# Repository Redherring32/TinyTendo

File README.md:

# Tiny 'Tendo
An open-source Gameboy sized handheld NES using real hardware

## DISCLAIMER:

TinyTendo is a complex project that has taken a ton of effort, and despite now being open source should still be considered somewhat experimental, should you find anything that isn't quite right, please file an issue.

Additionally, TinyTendo requires physically cutting and grinding ORIGINAL NES chips down smaller, this is a difficult, tedious, and risky process. 

You could KILL the chips if this is not done correctly, do this at your own risk, I am not responsible for damage to any hardware resulting from attempting to build this project.

## Repository Structure:

* Hardware: Contains all files relating to the hardware design for the various PCBs used for this project

* Software: Contains the software required for the brightness mod PCB

* 3D-CAD: Contains design files for the housing design

The files required to order PCBs can be found under releases.

This project is a derivitive of OpenTendo, and OpenTendo-Toploader, and is licensed accordingly. Please read the LICENSE in the repository for more info.

Since this project is open-source you may do as you like with it, whether that is to make TinyTendo for personal use, sell PCBs or assembled handhelds, or to use the provided info for further custom PCB work/designs.

*Note:* 
REAL NES chips from a real NES are required, clone chips cannot be used without some redesign of the motherboard, as they cannot be trimmed down as small.
A version of the PCB that supports them would be relatively easy to make, but I myself have no interest in doing so. (PRs to add a "clone" branch are welcome!)

And finally, I am NOT an EE, if you are at all disgusted by any aspect of the PCB designs, I am sorry. (PRs for this are also welcome :P)

## TO-DO:

* Write chip trimming guide to go over workflow and best practices

* Update readme image to reflect current hardware revision

* Figure out what I am forgetting to add to TO-DO

## License:

Licensed under
the TAPR Open Hardware License (www.tapr.org/OHL)

©Redherring32 2019-2022

All hardware contained within this repository was designed by me except the Brightness mod PCB.
The brightness mod PCB was designed by YveltalGriffin, and has been licensed under TAPR OHL with permission from the author.
The brightness PCB was designed using Eagle, all other hardware was designed using KiCAD.
The Brightness software was written by YveltalGriffin, and has been licensed under MIT with permission from the author, see LICENSE in software folder for details.
## Credits

In no particular order:

*FenrisWolfRetro* -Creating the wiring diagram in the Hardware folder.

*YveltalGriffin* -Designed the brightness mod PCB, and wrote the code for it, and was just a tremendous help.

*DiscoStarslayer* -Helping to inspire me to trim the chipset, without his joking suggestion to dremel the package and solder to the leads, I would not have started researching chip trimming.

*lidnariq* -Helping me diagnose my idiotic design blunders, might not have had the motivation to keep going on the project without their help.

*BucketMouse* -Designing cartridge PCBs for TinyTendo, and help with diagnosis work.

*MuraMasa* -Help with diagnosis work, sharing KiCAD footprints for early protos cause I kept messing mine up. :)

And to all of the awesome people in NESDev, you guys rock.

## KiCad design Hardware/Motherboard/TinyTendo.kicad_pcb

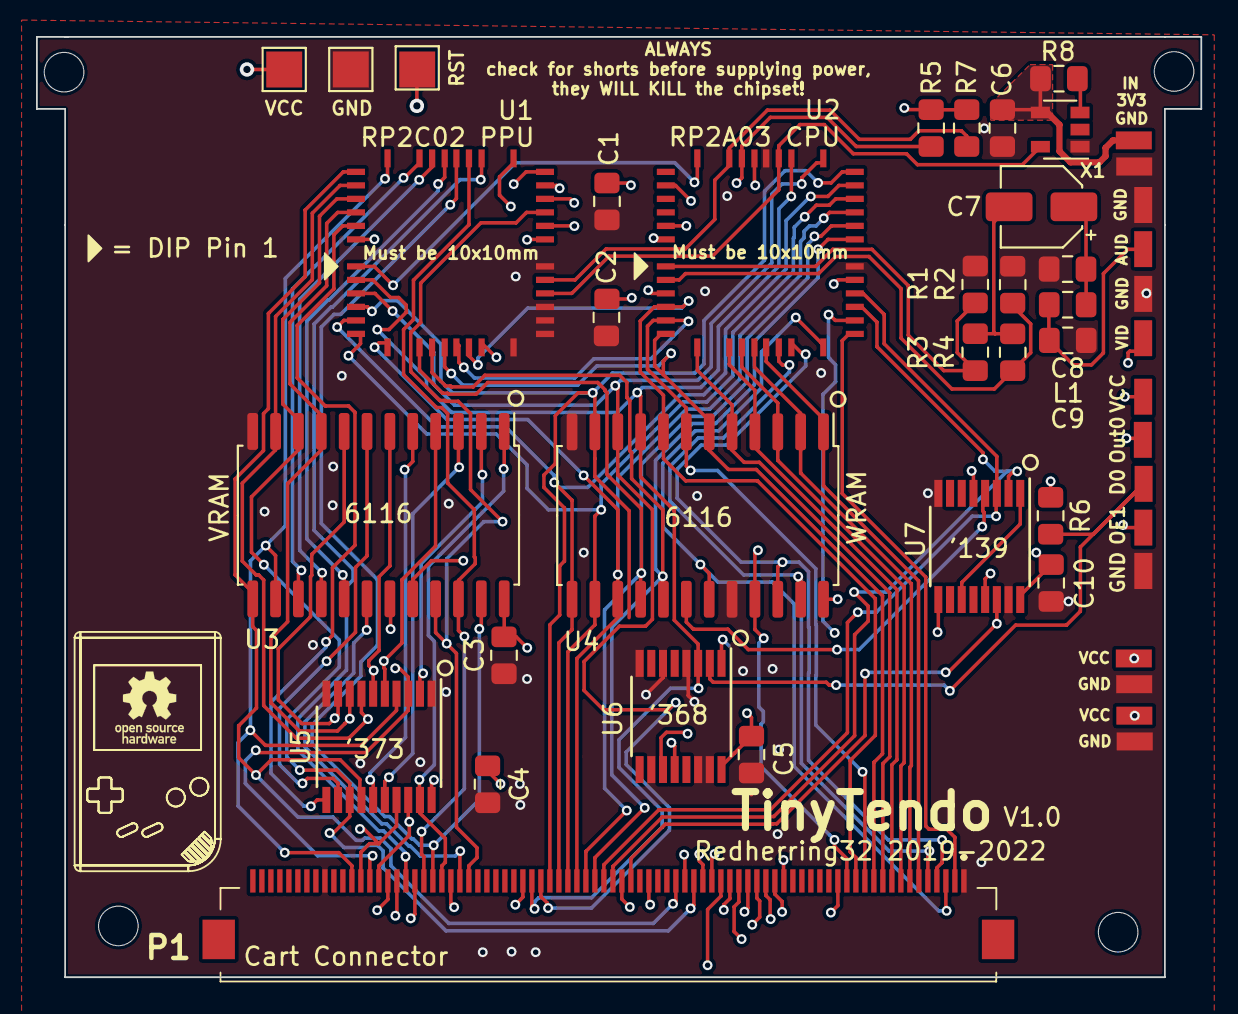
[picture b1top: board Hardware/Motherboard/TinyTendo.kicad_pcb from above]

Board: 4 copper layers, 64.7 x 52.2 mm, 50 parts (0 on the bottom side), 75 nets.

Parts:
C1, C2, C4, C5, C10: 10nF; C_0805_2012Metric_Pad1.15x1.40mm_HandSolder
C3, C6, C9: 0.1uF; C_0805_2012Metric_Pad1.15x1.40mm_HandSolder
C7: 1uF; CP_Elec_4x5.3
C8: 220pF; C_0805_2012Metric_Pad1.15x1.40mm_HandSolder
H1, H2, H3, H4: MountingHole_2.2mm_M2
J1, J2, J2#2, J2#3, J4#2, J5#2, J6, J6#2, J6#3, J6#4, J6#5, J7, J7#2, J8, J9: Conn_01x01_Male; SolderPad
J3, J4, J5: Conn_01x01_Male; TestPoint_Pad_2.0x2.0mm
L1: 39uH; L_0805_2012Metric_Pad1.15x1.40mm_HandSolder
P1: 72-Pin Connector; XF3M80151BE
R1, R2: 160; R_0805_2012Metric_Pad1.15x1.40mm_HandSolder
R3: 200; R_0805_2012Metric_Pad1.15x1.40mm_HandSolder
R4: 100; R_0805_2012Metric_Pad1.15x1.40mm_HandSolder
R5, R6, R7: 10K; R_0805_2012Metric_Pad1.15x1.40mm_HandSolder
R8: 1K; R_0805_2012Metric_Pad1.15x1.40mm_HandSolder
U1: RP2C02 PPU; Cut chip
U2: RP2A03 CPU; Cut chip
U3: 6116 (VRAM); SOIC-24W_7.5x15.4mm_P1.27mm
U4: 6116 (WRAM); SOIC-24W_7.5x15.4mm_P1.27mm
U5: 74HC373; TSSOP-20_4.4x6.5mm_P0.65mm
U6: 40H368 (CI); TSSOP-16_4.4x5mm_P0.65mm
U7: 74HC139; TSSOP-16_4.4x5mm_P0.65mm
X1: SiT2001B; SOT-23-5

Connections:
/3V3: C6.2, J1.1, R8.2, X1.4
/4016-D0: J4#2.1, R6.2, U6.2
/ALE: U1.39, U5.11
/AUDIO: C9.1, J8.1, L1.2
/CPU-A0: P1.13, U1.12, U2.4, U4.8
/CPU-A1: P1.12, U1.11, U2.5, U4.7
/CPU-A2: P1.11, U1.10, U2.6, U4.6
/CPU-A3: P1.10, U2.7, U4.5
/CPU-A4: P1.9, U2.8, U4.4
/CPU-A5: P1.8, U2.9, U4.3
/CPU-A6: P1.7, U2.10, U4.2
/CPU-A7: P1.6, U2.11, U4.1
/CPU-A8: P1.5, U2.12, U4.23
/CPU-A9: P1.4, U2.13, U4.22
/CPU-A10: P1.3, U2.14, U4.19
/CPU-A11: P1.2, U2.15
/CPU-A12: P1.39, U2.16
/CPU-A13: P1.40, U2.17, U7.2
/CPU-A14: P1.41, U2.18, U7.3
/CPU-A15: U2.19, U7.13
/CPU-D0: P1.49, U1.2, U2.28, U4.9, U6.3
/CPU-D1: P1.48, U1.3, U2.27, U4.10
/CPU-D2: P1.47, U1.4, U2.26, U4.11
/CPU-D3: P1.46, U1.5, U2.25, U4.13
/CPU-D4: P1.45, U1.6, U2.24, U4.14
/CPU-D5: P1.44, U1.7, U2.23, U4.15
/CPU-D6: P1.43, U1.8, U2.22, U4.16
/CPU-D7: P1.42, U1.9, U2.21, U4.17
/CPU-R~W: P1.14, U1.1, U2.34, U4.21
/GND: C1.1, C2.1, C3.1, C4.1, C5.1, C6.1, C8.1, C9.2, C10.1, J2.1, J2#2.1, J2#3.1, J3.1, J6#4.1, J7.1, J7#2.1, P1.1, P1.72, R1.1, R2.1, U1.14, U1.15, U1.16, U1.17, U1.20, U2.20, U2.30, U3.12, U4.12, U4.20, U5.1, U5.10, U6.4, U6.6, U6.8, U6.10, U6.14, U6.15, U7.8, U7.15, X1.1
/M2: P1.38, U2.31, U7.14
/OUT-0: J5#2.1, U2.39
/PPU-A0: P1.29, U3.8, U5.9
/PPU-A1: P1.28, U3.7, U5.12
/PPU-A2: P1.27, U3.6, U5.6
/PPU-A3: P1.26, U3.5, U5.15
/PPU-A4: P1.25, U3.4, U5.5
/PPU-A5: P1.24, U3.3, U5.16
/PPU-A6: P1.23, U3.2, U5.2
/PPU-A7: P1.59, U3.1, U5.19
/PPU-A8: P1.60, U1.30, U3.23
/PPU-A9: P1.61, U1.29, U3.22
/PPU-A10: P1.63, U1.28
/PPU-A11: P1.62, U1.27
/PPU-A12: P1.64, U1.26
/PPU-A13: P1.65, U1.25, U6.12
/PPU-D0: P1.30, U1.38, U3.9, U5.8
/PPU-D1: P1.31, U1.37, U3.10, U5.13
/PPU-D2: P1.32, U1.36, U3.11, U5.7
/PPU-D3: P1.33, U1.35, U3.13, U5.14
/PPU-D4: P1.69, U1.34, U3.14, U5.4
/PPU-D5: P1.68, U1.33, U3.15, U5.17
/PPU-D6: P1.67, U1.32, U3.16, U5.3
/PPU-D7: P1.66, U1.31, U3.17, U5.18
/PPU-~A13: P1.58, U6.11
/PPU-~CE: U1.13, U7.5
/PPU-~RD: P1.21, U1.24, U3.20
/PPU-~WE: P1.56, U1.23, U3.21
/SOUND-1: R1.2, R3.2, U2.1
/SOUND-2: R2.2, R4.2, U2.2
/SYS-CLK: U1.18, U2.29, X1.5
/VCC: C1.2, C2.2, C3.2, C4.2, C5.2, C10.2, J4.1, J6.1, J6#2.1, J6#3.1, P1.36, R5.1, R6.1, R7.1, U1.22, U1.40, U2.40, U3.24, U4.24, U5.20, U6.16, U7.16
/VIDEO: J9.1, U1.21
/VRAM-A10: P1.22, U3.19
/VRAM-~CE: P1.57, U3.18
/WRAM-~CE: U4.18, U7.4
/~IRQ: P1.15, R5.2, U2.32
/~NMI: R7.2, U1.19, U2.33
/~OE1: J6#5.1, U2.36, U6.1
/~ROMSEL: P1.50, U7.9
/~RST: J5.1, U2.3
unnamed: C7.1, C8.2, L1.1
unnamed: C7.2, R3.1, R4.1
unnamed: R8.1, X1.3
unnamed: U7.1, U7.11

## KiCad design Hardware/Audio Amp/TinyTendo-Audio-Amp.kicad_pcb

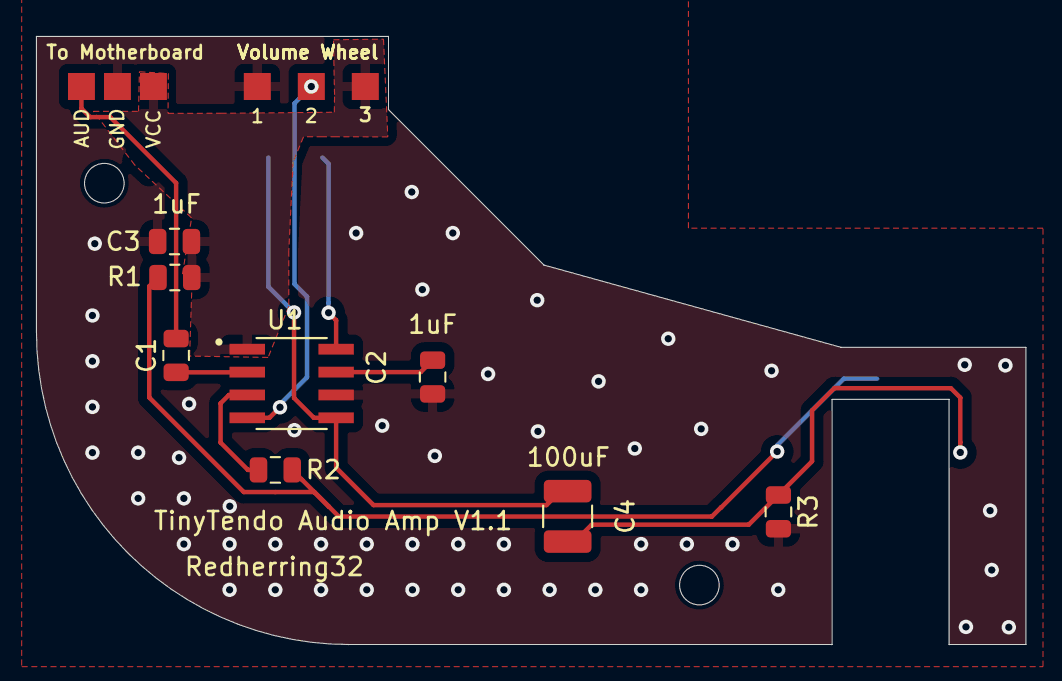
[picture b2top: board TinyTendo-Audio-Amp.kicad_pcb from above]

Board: 2 copper layers, 55.0 x 33.8 mm, 14 parts (0 on the bottom side), 11 nets.

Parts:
 : MountingHole_2.2mm_M2
 #2: MountingHole_2.2mm_M2
C1: 0.22uF; C_0805_2012Metric
C2, C3: 1uF; C_0805_2012Metric
C4: 100uF; C_1210_3225Metric
J1: Conn_Coaxial; AUD-IN
J2: MJ-3523-SMT; CUI_MJ-3523-SMT-Inline
LS1: Speaker
R1, R2: 100K; R_0805_2012Metric
R3: 150R; R_0805_2012Metric
U1: LM4865M; SOIC127P599X175-8N
Volume Wheel: 10K; VolPot

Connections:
/GND: C2.2, C3.2, J1.2, J2.1, R3.2, U1.6, Volume Wheel.3
/VDD: C3.1, J1.3, R1.1, U1.1, Volume Wheel.1
unnamed: C1.1, U1.2
unnamed: C1.2, J1.1
unnamed: C2.1, U1.7
unnamed: C4.1, LS1.1, U1.5
unnamed: C4.2, J2.2, R3.1
unnamed: J2.10, R1.2, R2.1
unnamed: LS1.2, U1.8
unnamed: R2.2, U1.3
unnamed: U1.4, Volume Wheel.2

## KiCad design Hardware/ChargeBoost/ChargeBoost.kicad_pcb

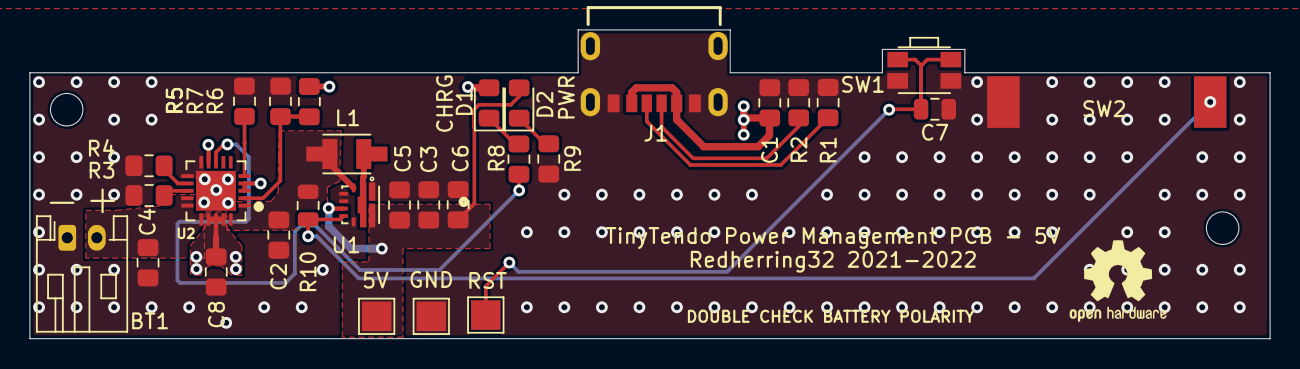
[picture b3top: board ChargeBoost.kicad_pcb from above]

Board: 2 copper layers, 84.0 x 20.9 mm, 32 parts (0 on the bottom side), 17 nets.

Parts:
 : MountingHole_2.2mm_M2
 #2: MountingHole_2.2mm_M2
BT1: 2800mAh; JST_PH_S2B-PH-K_1x02_P2.00mm_Horizontal-Mirrored
C1, C2, C4, C8: 10uF; C_0805_2012Metric_Pad1.15x1.40mm_HandSolder
C3, C5, C6: 22uF; C_0805_2012Metric_Pad1.15x1.40mm_HandSolder
C7: 1uF; C_0805_2012Metric
D1: Red; LED_0805_2012Metric_Pad1.15x1.40mm_HandSolder
D2: BLUE; LED_0805_2012Metric_Pad1.15x1.40mm_HandSolder
J1: USB4125-GF-A_REVA2; GCT_USB4125-GF-A_REVA2
J3, J4, J5: Conn_01x01_Male; TestPoint_Pad_2.0x2.0mm
L1: 1uH; IND_LQH32CN1R0M23L
R1, R2: 5K1; R_0805_2012Metric_Pad1.15x1.40mm_HandSolder
R3, R8: 1K; R_0805_2012Metric_Pad1.15x1.40mm_HandSolder
R4, R7: 100K; R_0805_2012Metric_Pad1.15x1.40mm_HandSolder
R5: 15K; R_0805_2012Metric_Pad1.15x1.40mm_HandSolder
R6: 270K; R_0805_2012Metric_Pad1.15x1.40mm_HandSolder
R9: 91R; R_0805_2012Metric_Pad1.15x1.40mm_HandSolder
R10: 200R; R_0805_2012Metric
SW1: SW_Push; SW_SPST_EVQP7A
SW2: PWR
U1: TPS61235PRWLT; CONV_TPS61235PRWLT
U2: MCP73871-2AAI_ML; QFN50P400X400X100-21N

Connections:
/GND: BT1.2, C1.2, C2.2, C3.2, C4.2, C5.2, C6.2, C7.2, C8.2, J1.A12, J1.B12, J1.S1, J3.1, R1.2, R2.2, R3.2, R4.2, R5.2, R7.2, R9.2, SW1.1, SW2.1, U1.1, U1.4, U1.5, U1.8, U2.10, U2.11, U2.21
/RST: C7.1, J5.1, SW1.2
/VBAT: C2.1, L1.1, R10.1, U1.3, U2.1, U2.20
/VBUS: C1.1, C8.1, D1.2, J1.A9, J1.B9, R6.1, U2.3, U2.4, U2.9, U2.17, U2.18, U2.19
/VOUT: C3.1, C5.1, C6.1, D2.2, J4.1, U1.6, U1.9
unnamed: BT1.1, C4.1, U2.14, U2.15, U2.16
unnamed: D1.1, R8.1
unnamed: D2.1, R9.1
unnamed: J1.A5, R2.1
unnamed: J1.B5, R1.1
unnamed: L1.2, U1.2
unnamed: R3.1, U2.13
unnamed: R4.1, U2.12
unnamed: R5.1, U2.5
unnamed: R6.2, R7.1, U2.2
unnamed: R8.2, U2.8
unnamed: R10.2, SW2.2, U1.7

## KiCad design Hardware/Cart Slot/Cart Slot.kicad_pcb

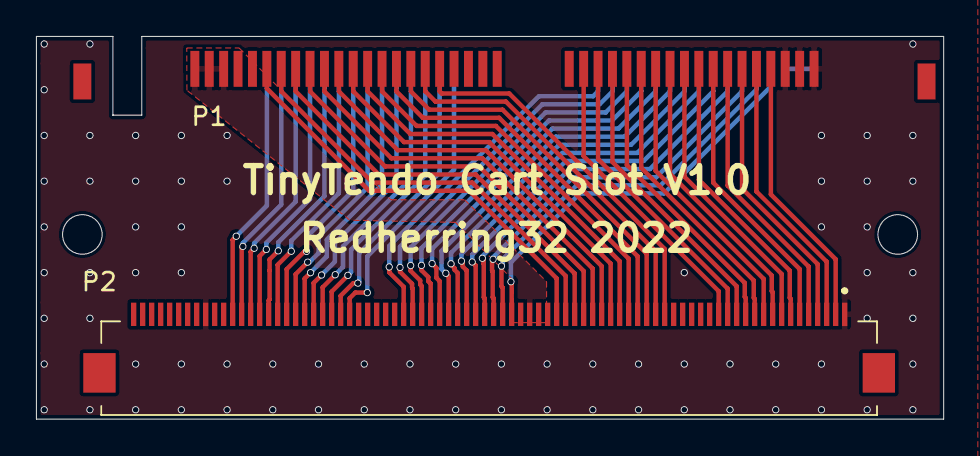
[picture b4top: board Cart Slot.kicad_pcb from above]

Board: 2 copper layers, 50.4 x 21.3 mm, 4 parts (0 on the bottom side), 56 nets.

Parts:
 : MountingHole_2.2mm_M2
 #2: MountingHole_2.2mm_M2
P1: 72-Pin Connector; Cart Slot
P2: 72-Pin Connector; XF3M80151BE

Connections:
/CPU-A0: P1.13, P2.13
/CPU-A1: P1.12, P2.12
/CPU-A2: P1.11, P2.11
/CPU-A3: P1.10, P2.10
/CPU-A4: P1.9, P2.9
/CPU-A5: P1.8, P2.8
/CPU-A6: P1.7, P2.7
/CPU-A7: P1.6, P2.6
/CPU-A8: P1.5, P2.5
/CPU-A9: P1.4, P2.4
/CPU-A10: P1.3, P2.3
/CPU-A11: P1.2, P2.2
/CPU-A12: P1.39, P2.39
/CPU-A13: P1.40, P2.40
/CPU-A14: P1.41, P2.41
/CPU-D0: P1.49, P2.49
/CPU-D1: P1.48, P2.48
/CPU-D2: P1.47, P2.47
/CPU-D3: P1.46, P2.46
/CPU-D4: P1.45, P2.45
/CPU-D5: P1.44, P2.44
/CPU-D6: P1.43, P2.43
/CPU-D7: P1.42, P2.42
/CPU-R~W: P1.14, P2.14
/GND: P1.1, P1.72, P2.1, P2.72
/M2: P1.38, P2.38
/PPU-A0: P1.29, P2.29
/PPU-A1: P1.28, P2.28
/PPU-A2: P1.27, P2.27
/PPU-A3: P1.26, P2.26
/PPU-A4: P1.25, P2.25
/PPU-A5: P1.24, P2.24
/PPU-A6: P1.23, P2.23
/PPU-A7: P1.59, P2.59
/PPU-A8: P1.60, P2.60
/PPU-A9: P1.61, P2.61
/PPU-A10: P1.63, P2.63
/PPU-A11: P1.62, P2.62
/PPU-A12: P1.64, P2.64
/PPU-A13: P1.65, P2.65
/PPU-D0: P1.30, P2.30
/PPU-D1: P1.31, P2.31
/PPU-D2: P1.32, P2.32
/PPU-D3: P1.33, P2.33
/PPU-D4: P1.69, P2.69
/PPU-D5: P1.68, P2.68
/PPU-D6: P1.67, P2.67
/PPU-D7: P1.66, P2.66
/PPU-~A13: P1.58, P2.58
/PPU-~RD: P1.21, P2.21
/PPU-~WE: P1.56, P2.56
/VCC: P1.36, P2.36
/VRAM-A10: P1.22, P2.22
/VRAM-~CE: P1.57, P2.57
/~IRQ: P1.15, P2.15
/~ROMSEL: P1.50, P2.50

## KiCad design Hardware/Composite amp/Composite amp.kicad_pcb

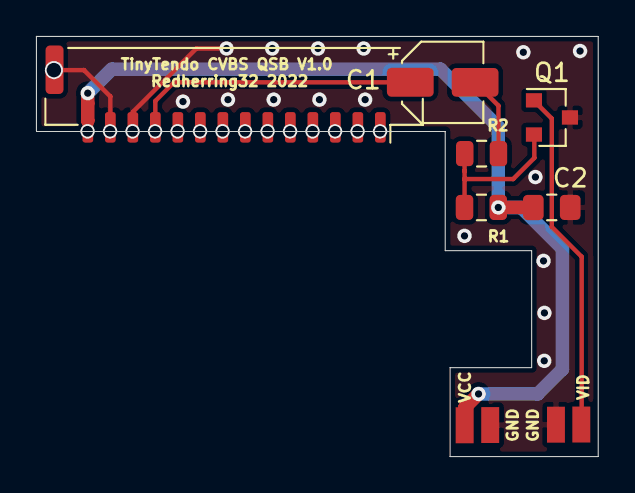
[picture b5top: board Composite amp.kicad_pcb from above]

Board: 2 copper layers, 31.2 x 23.3 mm, 10 parts (0 on the bottom side), 6 nets.

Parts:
C1: 100uF; CP_Elec_4x4.5
C2: 22uF; C_0805_2012Metric_Pad1.15x1.40mm_HandSolder
GND1, GND2: TestPoint; SolderPad
J1: Conn_01x14_Female; JST_GH_SM14B-GHS-TB_1x14-1MP_P1.25mm_Horizontal
Q1: MMBT3906; SOT-23
R1: 300R; R_0805_2012Metric
R2: 110R; R_0805_2012Metric
VCC1: TestPoint; SolderPad
VID1: TestPoint; SolderPad

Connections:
/5V: C2.1, J1.14, R1.1, VCC1.1
/GND: C2.2, GND1.1, GND2.1, J1.12, J1.13, Q1.3
/VIDEO-IN: Q1.1, VID1.1
/VIDEO-OUT: C1.1, J1.11
unnamed: C1.2, R2.1
unnamed: Q1.2, R1.2, R2.2

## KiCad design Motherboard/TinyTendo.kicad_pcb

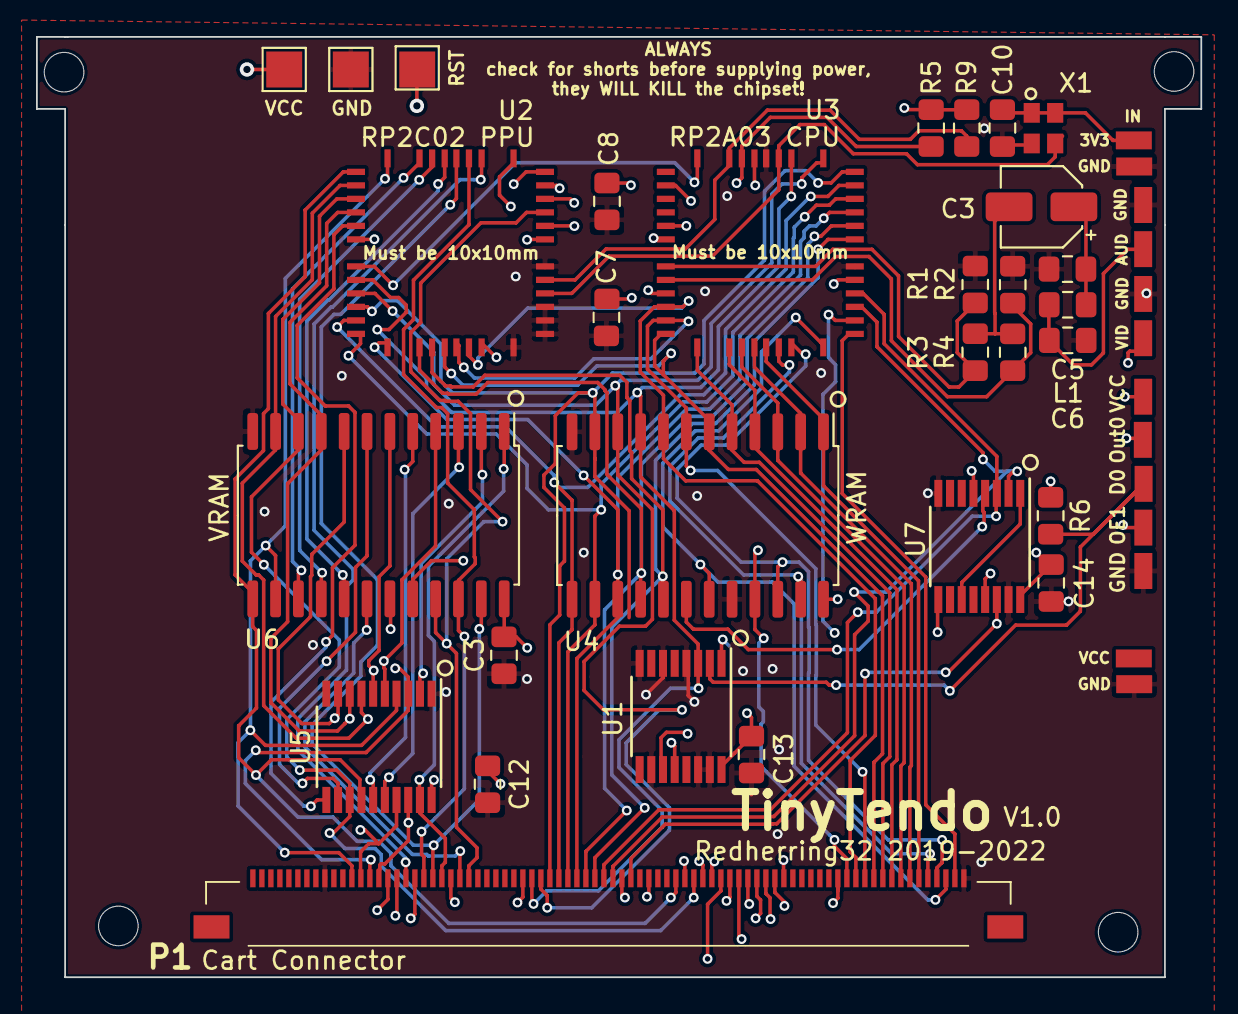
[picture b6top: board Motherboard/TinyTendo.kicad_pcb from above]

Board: 4 copper layers, 64.7 x 52.2 mm, 47 parts (0 on the bottom side), 74 nets.

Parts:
C3: 1uF; CP_Elec_4x5.3
C3#2, C6, C7, C8, C12, C13, C14: 10nF; C_0805_2012Metric_Pad1.15x1.40mm_HandSolder
C5: 220pF; C_0805_2012Metric_Pad1.15x1.40mm_HandSolder
C10: 0.1uF; C_0805_2012Metric_Pad1.15x1.40mm_HandSolder
H1, H2, H3, H4: MountingHole_2.2mm_M2
J1, J2, J2#2, J4#2, J5#2, J6, J6#2, J6#3, J6#4, J7, J7#2, J8, J9: Conn_01x01_Male; SolderPad
J3, J4, J5: Conn_01x01_Male; TestPoint_Pad_2.0x2.0mm
L1: 39u; L_0805_2012Metric_Pad1.15x1.40mm_HandSolder
P1: 72-Pin Connector; 5051108091
R1, R2: 160; R_0805_2012Metric_Pad1.15x1.40mm_HandSolder
R3: 200; R_0805_2012Metric_Pad1.15x1.40mm_HandSolder
R4: 100; R_0805_2012Metric_Pad1.15x1.40mm_HandSolder
R5, R6, R9: 10K; R_0805_2012Metric_Pad1.15x1.40mm_HandSolder
U1: 40H368 (CI); TSSOP-16_4.4x5mm_P0.65mm
U2: RP2C02 PPU; Cut chip
U3: RP2A03 CPU; Cut chip
U4: 6116 (WRAM); SOIC-24W_7.5x15.4mm_P1.27mm
U5: 74HC373; TSSOP-20_4.4x6.5mm_P0.65mm
U6: 6116 (VRAM); SOIC-24W_7.5x15.4mm_P1.27mm
U7: 74HC139; TSSOP-16_4.4x5mm_P0.65mm
X1: SG-8018CG-TJHPAB; Oscillator

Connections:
/3V3: C10.1, J1.1, X1.1, X1.4
/4016-D0: J4#2.1, R6.2, U1.2
/ALE: U2.39, U5.11
/AUDIO: C6.1, J8.1, L1.2
/CPU-A0: P1.13, U2.12, U3.4, U4.8
/CPU-A1: P1.12, U2.11, U3.5, U4.7
/CPU-A2: P1.11, U2.10, U3.6, U4.6
/CPU-A3: P1.10, U3.7, U4.5
/CPU-A4: P1.9, U3.8, U4.4
/CPU-A5: P1.8, U3.9, U4.3
/CPU-A6: P1.7, U3.10, U4.2
/CPU-A7: P1.6, U3.11, U4.1
/CPU-A8: P1.5, U3.12, U4.23
/CPU-A9: P1.4, U3.13, U4.22
/CPU-A10: P1.3, U3.14, U4.19
/CPU-A11: P1.2, U3.15
/CPU-A12: P1.39, U3.16
/CPU-A13: P1.40, U3.17, U7.2
/CPU-A14: P1.41, U3.18, U7.3
/CPU-A15: U3.19, U7.13
/CPU-D0: P1.49, U1.3, U2.2, U3.28, U4.9
/CPU-D1: P1.48, U2.3, U3.27, U4.10
/CPU-D2: P1.47, U2.4, U3.26, U4.11
/CPU-D3: P1.46, U2.5, U3.25, U4.13
/CPU-D4: P1.45, U2.6, U3.24, U4.14
/CPU-D5: P1.44, U2.7, U3.23, U4.15
/CPU-D6: P1.43, U2.8, U3.22, U4.16
/CPU-D7: P1.42, U2.9, U3.21, U4.17
/CPU-R~W: P1.14, U2.1, U3.34, U4.21
/GND: C3#2.1, C5.1, C6.2, C7.1, C8.1, C10.2, C12.1, C13.1, C14.1, J2.1, J2#2.1, J3.1, J6#3.1, J7.1, J7#2.1, P1.1, P1.72, R1.1, R2.1, U1.4, U1.6, U1.8, U1.10, U1.14, U1.15, U2.14, U2.15, U2.16, U2.17, U2.20, U3.20, U3.30, U4.12, U4.20, U5.1, U5.10, U6.12, U7.8, U7.15, X1.2
/M2: P1.38, U3.31, U7.14
/OUT-0: J5#2.1, U3.39
/PPU-A0: P1.29, U5.9, U6.8
/PPU-A1: P1.28, U5.12, U6.7
/PPU-A2: P1.27, U5.6, U6.6
/PPU-A3: P1.26, U5.15, U6.5
/PPU-A4: P1.25, U5.5, U6.4
/PPU-A5: P1.24, U5.16, U6.3
/PPU-A6: P1.23, U5.2, U6.2
/PPU-A7: P1.59, U5.19, U6.1
/PPU-A8: P1.60, U2.30, U6.23
/PPU-A9: P1.61, U2.29, U6.22
/PPU-A10: P1.63, U2.28
/PPU-A11: P1.62, U2.27
/PPU-A12: P1.64, U2.26
/PPU-A13: P1.65, U1.12, U2.25
/PPU-D0: P1.30, U2.38, U5.8, U6.9
/PPU-D1: P1.31, U2.37, U5.13, U6.10
/PPU-D2: P1.32, U2.36, U5.7, U6.11
/PPU-D3: P1.33, U2.35, U5.14, U6.13
/PPU-D4: P1.69, U2.34, U5.4, U6.14
/PPU-D5: P1.68, U2.33, U5.17, U6.15
/PPU-D6: P1.67, U2.32, U5.3, U6.16
/PPU-D7: P1.66, U2.31, U5.18, U6.17
/PPU-~A13: P1.58, U1.11
/PPU-~CE: U2.13, U7.5
/PPU-~RD: P1.21, U2.24, U6.20
/PPU-~WE: P1.56, U2.23, U6.21
/SOUND-1: R1.2, R3.2, U3.1
/SOUND-2: R2.2, R4.2, U3.2
/SYS-CLK: U2.18, U3.29, X1.3
/VCC: C3#2.2, C7.2, C8.2, C12.2, C13.2, C14.2, J4.1, J6.1, J6#2.1, P1.36, R5.1, R6.1, R9.1, U1.16, U2.22, U2.40, U3.40, U4.24, U5.20, U6.24, U7.16
/VIDEO: J9.1, U2.21
/VRAM-A10: P1.22, U6.19
/VRAM-~CE: P1.57, U6.18
/WRAM-~CE: U4.18, U7.4
/~IRQ: P1.15, R5.2, U3.32
/~NMI: R9.2, U2.19, U3.33
/~OE1: J6#4.1, U1.1, U3.36
/~ROMSEL: P1.50, U7.9
/~RST: J5.1, U3.3
unnamed: C3.1, C5.2, L1.1
unnamed: C3.2, R3.1, R4.1
unnamed: U7.1, U7.11

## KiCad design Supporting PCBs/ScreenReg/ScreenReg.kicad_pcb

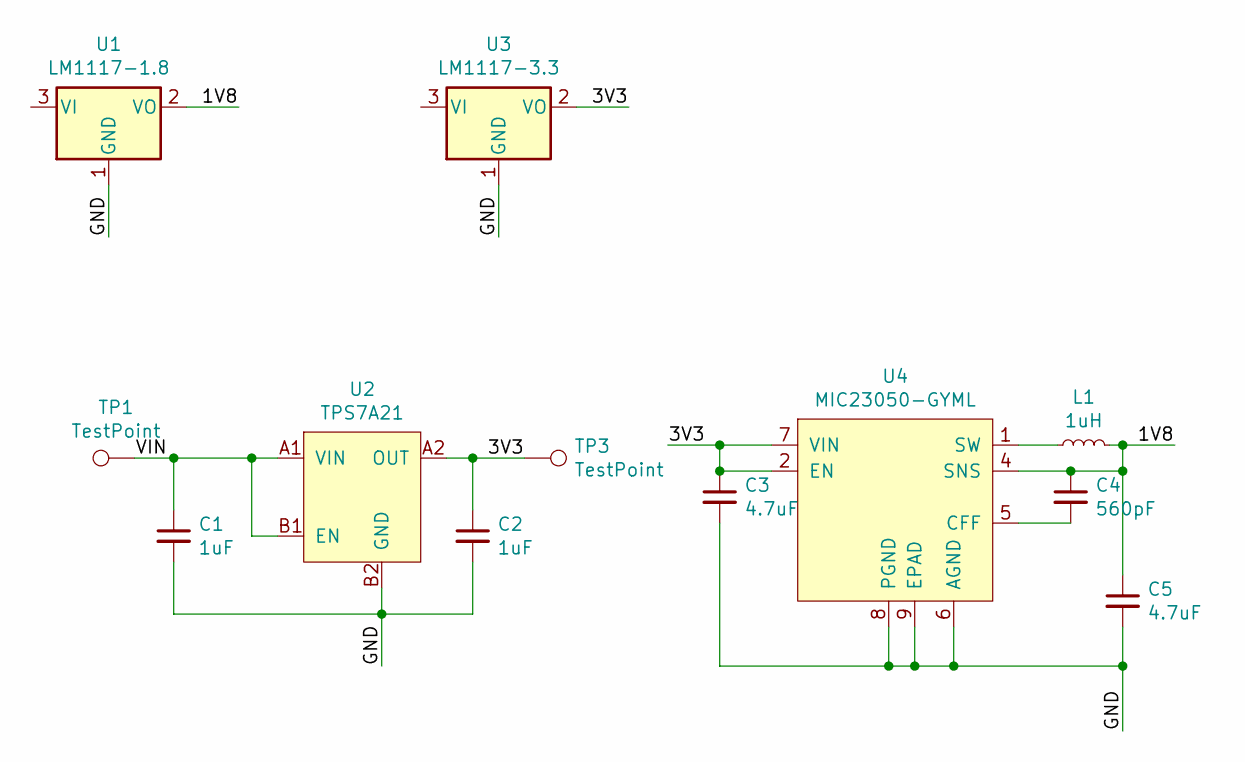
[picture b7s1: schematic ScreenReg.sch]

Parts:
C1, C2: 1uF; C_0402_1005Metric
C3, C5: 4.7uF; C_0402_1005Metric
C4: 560pF; C_0402_1005Metric
L1: 1uH; L_0402_1005Metric
TP1, TP3: TestPoint; TestPoint_Pad_1.5x1.5mm
U1: LM1117-1.8; SOT-223
U2: TPS7A21
U3: LM1117-3.3; SOT-223
U4: MIC23050-GYML; Micrel_MLF-8-1EP_2x2mm_P0.5mm_EP0.8x1.3mm_ThermalVias

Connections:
/1V8: C4.1, C5.1, L1.2, U1.2 (VO), U4.4 (SNS)
/3V3: C2.1, C3.1, TP3.1, U2.A2 (OUT), U3.2 (VO), U4.2 (EN), U4.7 (VIN)
/GND: C1.2, C2.2, C3.2, C5.2, U1.1 (GND), U2.B2 (GND), U3.1 (GND), U4.6 (AGND), U4.8 (PGND), U4.9 (EPAD)
/VIN: C1.1, TP1.1, U2.A1 (VIN), U2.B1 (EN)
unnamed: C4.2, U4.5 (CFF)
unnamed: L1.1, U4.1 (SW)

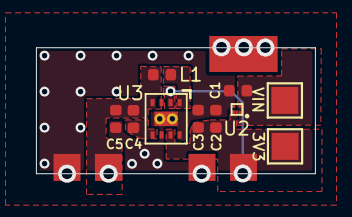
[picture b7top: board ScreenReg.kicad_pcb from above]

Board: 2 copper layers, 15.5 x 7.0 mm, 12 parts (0 on the bottom side), 6 nets.

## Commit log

2022-05-28 + Add Working Files + Initial Readme Draft
2022-05-29 + Updated README.md + Fixed schematic/pinout error with Q1, and added decoupling capacitor to Composite Amp
2022-06-15 + Motherboard is now V1.0 + Redesigned ScreenReg for improved reliability + Added both versions of ChargeBoost + Remove now redundant files/directories
2022-08-25 +Remove redundant files
2022-08-25 Update TO-DO
2022-09-04 Rename Motherboard.md to readme.md
2022-09-04 + Added TinyTendo Cart Shell CAD files
2022-09-06 + Updated FFC footprint on Cart Slot and Cart-Test
2022-09-06 Fixed typo, whoops!
2022-09-06 Update README.md
    Update Credits
    Update To-do
2022-09-14 Redid ChargeBoost layout, and added EN pull up, and RST capacitor
2022-10-01 + Fixed error on InCU1 layer + Added missing pads for audio amp power + Removed redundant autosave files
2022-11-20 +Update Motherboard to use more available SiT2001B oscillator.
2023-03-31 + Fixed isue where Cart slot would strain screwposts overtime + Updated Cartridge shell design to make printing easier, and make room for TNY-TKROM boards
2024-01-18 + Corrected duplicate reference error in Chargeboost.sch
    + Made changes to Audio Amp PCB to improve screwpost locations
    + Made changes to Button PCB to improve screwpost locations
    + Moved screen up 6mm to even out bezels on shell
    + Altered shell to improve screwpost placement, and add optional suppport for threaded inserts
    + Added 2 new shell variants, 1 with a logo via multicolor printing and threaded inserts, 1 with just threaded inserts
